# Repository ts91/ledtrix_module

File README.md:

# Ledtrix, a fully modular 16x16 LED matrix

Tileable and low profile (less than 1cm) for display applications. Can be used in an artsy clock. Each single LED is source/sink driven by a pair of transistors.

The transistors are controlled by shift-registers. There are 4 daisy-chained shift-registers with each 8 outputs giving the required 16 rows and 16 columns drive signals.

## Tileable
The outline of the unit is the same as 4 LED modules in a 2x2 configuration. This makes it possible to seamlessly tile the Ledtrix along any of its four edges.

Signals travel through the board from the left to the right indicated by the arrow and socket. The boards are soldered together by edge connectors. Soldering all of these gives a sturdy unit.

### Mounting holes
There are four mount holes on the back. It is impossible to reach these holes once the LED modules have been soldered onto the PCB. They can be used with press fit mount stages.

## Driving the Ledtrix
This can be tricky as the focus has been to make the PCB routing as simple as possible. Some thought must be put into it.
## Pictures

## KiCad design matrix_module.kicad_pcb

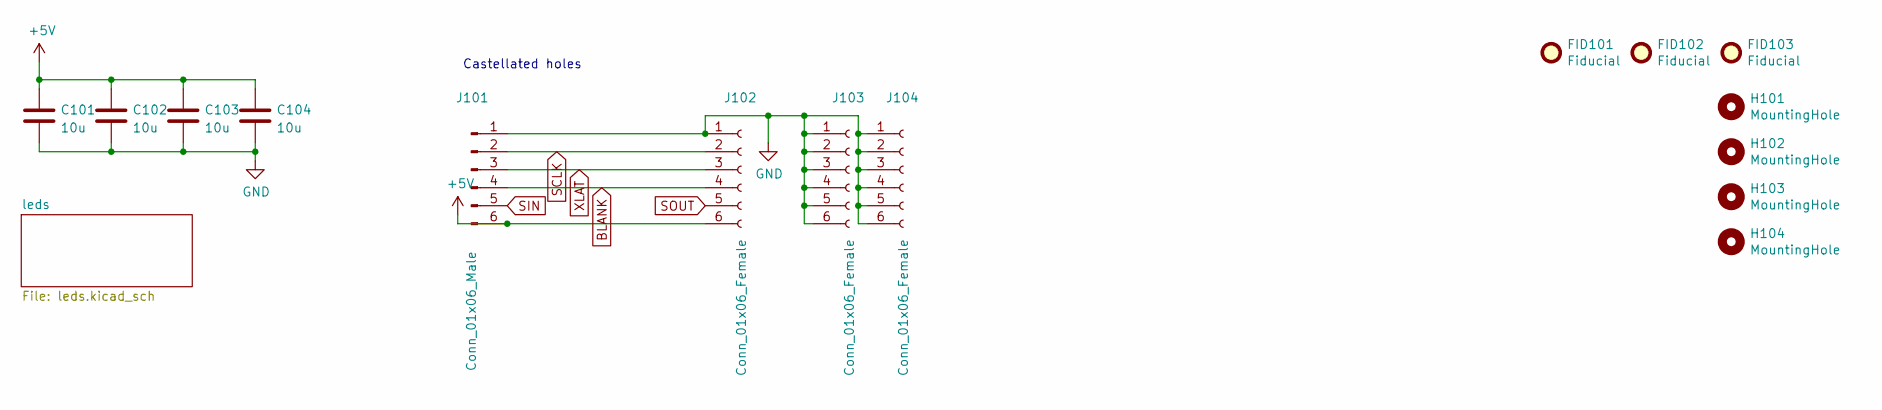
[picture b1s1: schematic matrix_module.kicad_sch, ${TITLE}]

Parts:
C101, C102, C103, C104: 10u; C_0805_2012Metric
FID101, FID102, FID103: Fiducial; Fiducial_0.5mm_Dia_1mm_Outer
H101, H102, H103, H104: MountingHole; MountingHole_2.2mm_M2
J101: Conn_01x06_Male; CastellatedEdge_1x06P3.175mm_Vertical
J102, J103, J104: Conn_01x06_Female; CastellatedEdge_1x06P3.175mm_Vertical

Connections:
+5V: C101.1, C102.1, C103.1, C104.1, J101.6, J102.6; also elsewhere on the board
BLANK: J101.4, J102.4; also elsewhere on the board
GND: C101.2, C102.2, C103.2, C104.2, J101.1, J102.1, J103.1, J103.2, J103.3, J103.4, J103.5, J103.6, J104.1, J104.2, J104.3, J104.4, J104.5, J104.6; also elsewhere on the board
SCLK: J101.2, J102.2; also elsewhere on the board
SIN: J101.5; also elsewhere on the board
SOUT: J102.5; also elsewhere on the board
XLAT: J101.3, J102.3; also elsewhere on the board

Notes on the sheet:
Castellated holes

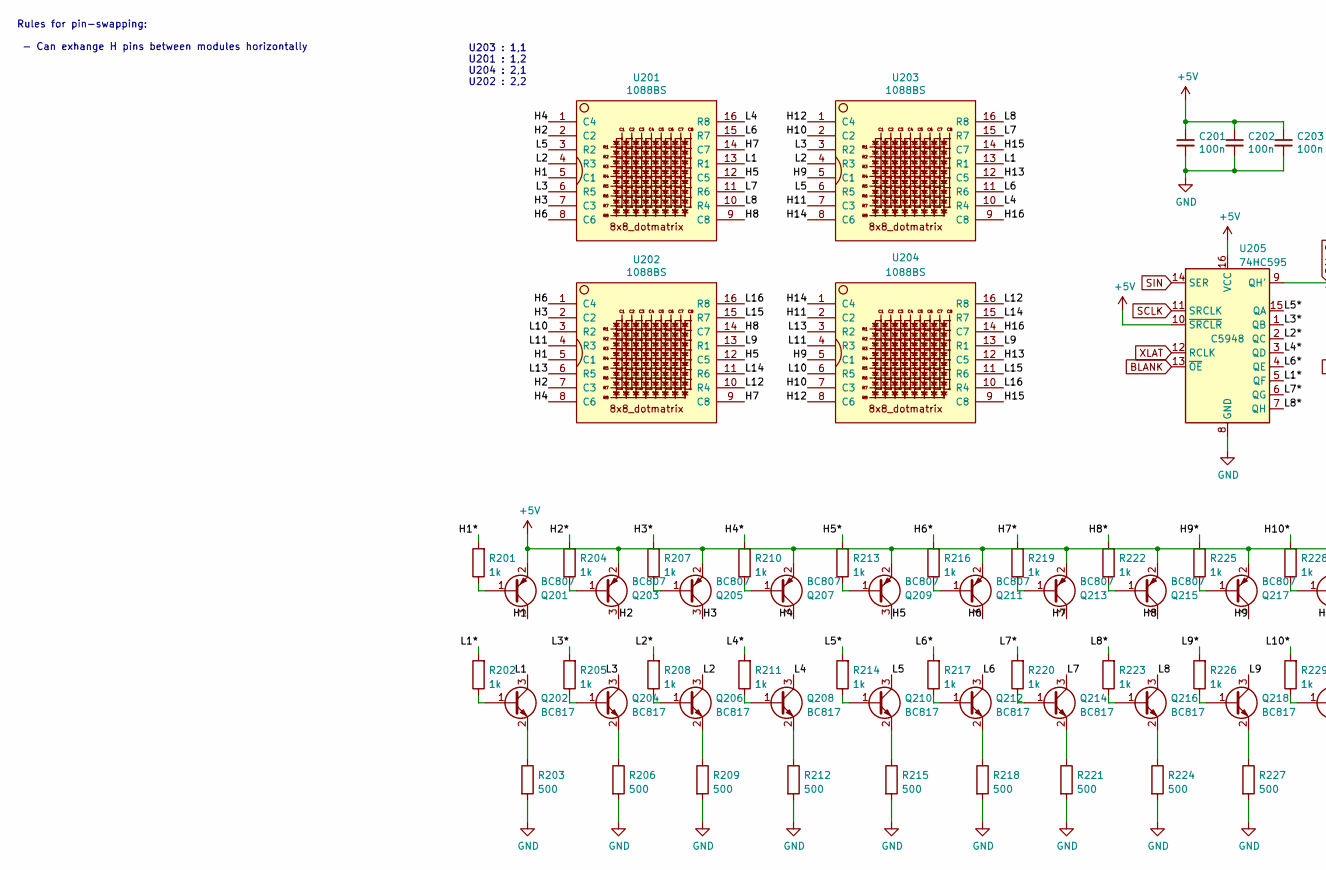
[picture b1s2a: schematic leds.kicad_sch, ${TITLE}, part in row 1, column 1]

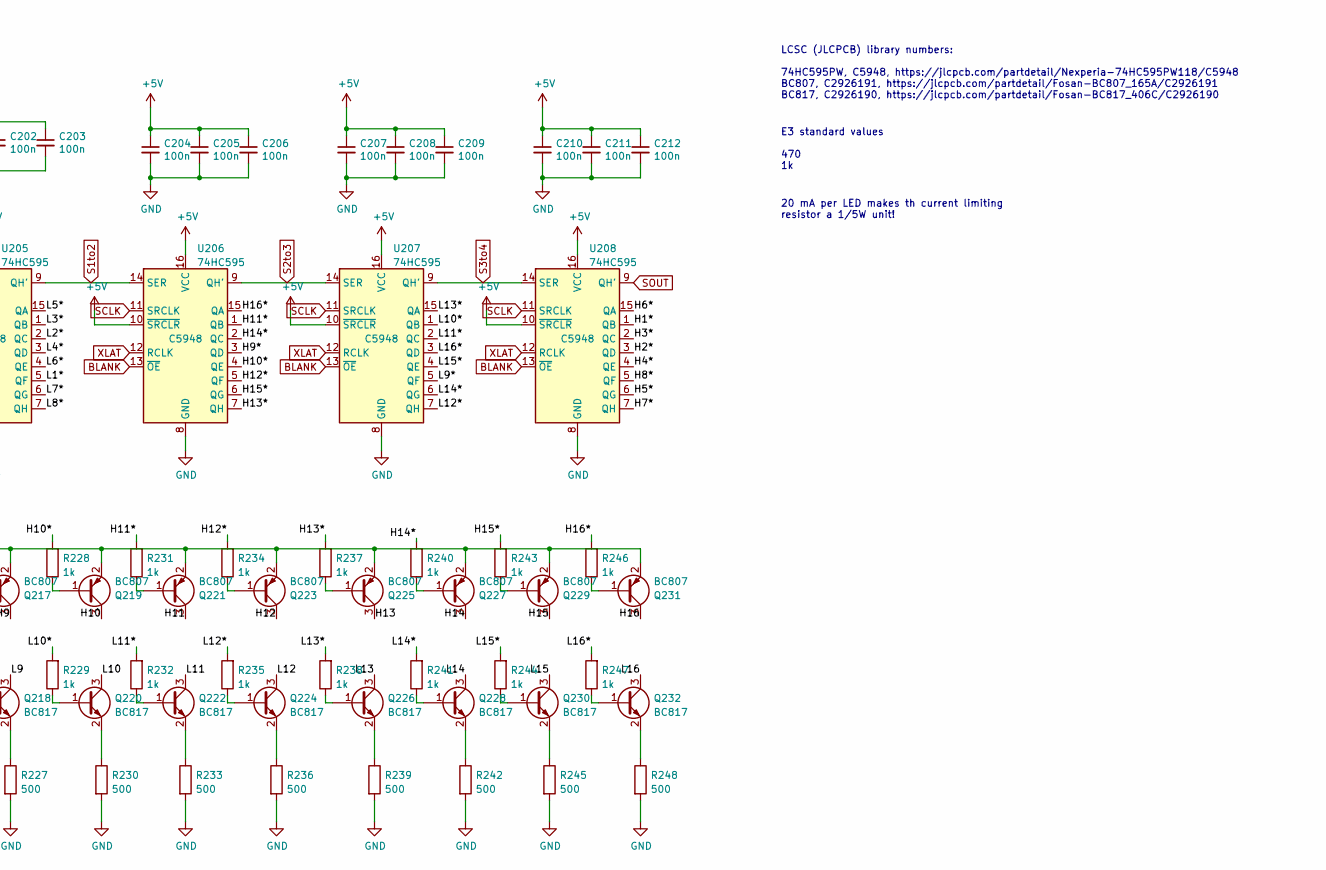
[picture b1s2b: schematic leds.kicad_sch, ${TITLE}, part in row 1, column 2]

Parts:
C201, C202, C203, C204, C205, C206, C207, C208, C209, C210, C211, C212: 100n; C_0603_1608Metric
Q201, Q203, Q205, Q207, Q209, Q211, Q213, Q215, Q217, Q219, Q221, Q223, Q225, Q227, Q229, Q231: BC807; SOT-23
Q202, Q204, Q206, Q208, Q210, Q212, Q214, Q216, Q218, Q220, Q222, Q224, Q226, Q228, Q230, Q232: BC817; SOT-23
R201, R202, R204, R205, R207, R208, R210, R211, R213, R214, R216, R217, R219, R220, R222, R223, R225, R226, R228, R229, R231, R232, R234, R235, R237, R238, R240, R241, R243, R244, R246, R247: 1k; R_0603_1608Metric
R203, R206, R209, R212, R215, R218, R221, R224, R227, R230, R233, R236, R239, R242, R245, R248: 500; R_0603_1608Metric
U201, U202, U203, U204: 1088BS; 8x8_dotmatrix_1088
U205, U206, U207, U208: 74HC595; TSSOP-16_4.4x5mm_P0.65mm; LCSC C5948

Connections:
+5V: C201.1, C202.1, C203.1, C204.1, C205.1, C206.1, C207.1, C208.1, C209.1, C210.1, C211.1, C212.1, Q201.2 (E), Q203.2 (E), Q205.2 (E), Q207.2 (E), Q209.2 (E), Q211.2 (E), Q213.2 (E), Q215.2 (E), Q217.2 (E), Q219.2 (E), Q221.2 (E), Q223.2 (E), Q225.2 (E), Q227.2 (E), Q229.2 (E), Q231.2 (E), U205.10 (~SRCLR), U205.16 (VCC), U206.10 (~SRCLR), U206.16 (VCC), U207.10 (~SRCLR), U207.16 (VCC), U208.10 (~SRCLR), U208.16 (VCC); also elsewhere on the board
/leds/H1: Q201.3 (C), U201.5 (C1), U202.5 (C1)
/leds/H1*: R201.2, U208.1 (QB)
/leds/H2: Q203.3 (C), U201.2 (C2), U202.7 (C3)
/leds/H2*: R204.2, U208.3 (QD)
/leds/H3: Q205.3 (C), U201.7 (C3), U202.2 (C2)
/leds/H3*: R207.2, U208.2 (QC)
/leds/H4: Q207.3 (C), U201.1 (C4), U202.8 (C6)
/leds/H4*: R210.2, U208.4 (QE)
/leds/H5: Q209.3 (C), U201.12 (C5), U202.12 (C5)
/leds/H5*: R213.2, U208.6 (QG)
/leds/H6: Q211.3 (C), U201.8 (C6), U202.1 (C4)
/leds/H6*: R216.2, U208.15 (QA)
/leds/H7: Q213.3 (C), U201.14 (C7), U202.9 (C8)
/leds/H7*: R219.2, U208.7 (QH)
/leds/H8: Q215.3 (C), U201.9 (C8), U202.14 (C7)
/leds/H8*: R222.2, U208.5 (QF)
/leds/H9: Q217.3 (C), U203.5 (C1), U204.5 (C1)
/leds/H9*: R225.2, U206.3 (QD)
/leds/H10: Q219.3 (C), U203.2 (C2), U204.7 (C3)
/leds/H10*: R228.2, U206.4 (QE)
/leds/H11: Q221.3 (C), U203.7 (C3), U204.2 (C2)
/leds/H11*: R231.2, U206.1 (QB)
/leds/H12: Q223.3 (C), U203.1 (C4), U204.8 (C6)
/leds/H12*: R234.2, U206.5 (QF)
/leds/H13: Q225.3 (C), U203.12 (C5), U204.12 (C5)
/leds/H13*: R237.2, U206.7 (QH)
/leds/H14: Q227.3 (C), U203.8 (C6), U204.1 (C4)
/leds/H14*: R240.2, U206.2 (QC)
/leds/H15: Q229.3 (C), U203.14 (C7), U204.9 (C8)
/leds/H15*: R243.2, U206.6 (QG)
/leds/H16: Q231.3 (C), U203.9 (C8), U204.14 (C7)
/leds/H16*: R246.2, U206.15 (QA)
/leds/L1: Q202.3 (C), U201.13 (R1), U203.13 (R1)
/leds/L1*: R202.2, U205.5 (QF)
/leds/L2: Q206.3 (C), U201.4 (R3), U203.4 (R3)
/leds/L2*: R208.2, U205.2 (QC)
/leds/L3: Q204.3 (C), U201.6 (R5), U203.3 (R2)
/leds/L3*: R205.2, U205.1 (QB)
/leds/L4: Q208.3 (C), U201.16 (R8), U203.10 (R4)
/leds/L4*: R211.2, U205.3 (QD)
/leds/L5: Q210.3 (C), U201.3 (R2), U203.6 (R5)
/leds/L5*: R214.2, U205.15 (QA)
/leds/L6: Q212.3 (C), U201.15 (R7), U203.11 (R6)
/leds/L6*: R217.2, U205.4 (QE)
/leds/L7: Q214.3 (C), U201.11 (R6), U203.15 (R7)
/leds/L7*: R220.2, U205.6 (QG)
/leds/L8: Q216.3 (C), U201.10 (R4), U203.16 (R8)
/leds/L8*: R223.2, U205.7 (QH)
/leds/L9: Q218.3 (C), U202.13 (R1), U204.13 (R1)
/leds/L9*: R226.2, U207.5 (QF)
/leds/L10: Q220.3 (C), U202.3 (R2), U204.6 (R5)
/leds/L10*: R229.2, U207.1 (QB)
/leds/L11: Q222.3 (C), U202.4 (R3), U204.4 (R3)
/leds/L11*: R232.2, U207.2 (QC)
/leds/L12: Q224.3 (C), U202.10 (R4), U204.16 (R8)
/leds/L12*: R235.2, U207.7 (QH)
/leds/L13: Q226.3 (C), U202.6 (R5), U204.3 (R2)
/leds/L13*: R238.2, U207.15 (QA)
/leds/L14: Q228.3 (C), U202.11 (R6), U204.15 (R7)
/leds/L14*: R241.2, U207.6 (QG)
/leds/L15: Q230.3 (C), U202.15 (R7), U204.11 (R6)
/leds/L15*: R244.2, U207.4 (QE)
/leds/L16: Q232.3 (C), U202.16 (R8), U204.10 (R4)
/leds/L16*: R247.2, U207.3 (QD)
BLANK: U205.13 (~OE), U206.13 (~OE), U207.13 (~OE), U208.13 (~OE); also elsewhere on the board
GND: C201.2, C202.2, C203.2, C204.2, C205.2, C206.2, C207.2, C208.2, C209.2, C210.2, C211.2, C212.2, R203.2, R206.2, R209.2, R212.2, R215.2, R218.2, R221.2, R224.2, R227.2, R230.2, R233.2, R236.2, R239.2, R242.2, R245.2, R248.2, U205.8 (GND), U206.8 (GND), U207.8 (GND), U208.8 (GND); also elsewhere on the board
unnamed: Q201.1 (B), R201.1
unnamed: Q202.1 (B), R202.1
unnamed: Q202.2 (E), R203.1
unnamed: Q203.1 (B), R204.1
unnamed: Q204.1 (B), R205.1
unnamed: Q204.2 (E), R206.1
unnamed: Q205.1 (B), R207.1
unnamed: Q206.1 (B), R208.1
unnamed: Q206.2 (E), R209.1
unnamed: Q207.1 (B), R210.1
unnamed: Q208.1 (B), R211.1
unnamed: Q208.2 (E), R212.1
unnamed: Q209.1 (B), R213.1
unnamed: Q210.1 (B), R214.1
unnamed: Q210.2 (E), R215.1
unnamed: Q211.1 (B), R216.1
unnamed: Q212.1 (B), R217.1
unnamed: Q212.2 (E), R218.1
unnamed: Q213.1 (B), R219.1
unnamed: Q214.1 (B), R220.1
unnamed: Q214.2 (E), R221.1
unnamed: Q215.1 (B), R222.1
unnamed: Q216.1 (B), R223.1
unnamed: Q216.2 (E), R224.1
unnamed: Q217.1 (B), R225.1
unnamed: Q218.1 (B), R226.1
unnamed: Q218.2 (E), R227.1
unnamed: Q219.1 (B), R228.1
unnamed: Q220.1 (B), R229.1
unnamed: Q220.2 (E), R230.1
unnamed: Q221.1 (B), R231.1
unnamed: Q222.1 (B), R232.1
unnamed: Q222.2 (E), R233.1
unnamed: Q223.1 (B), R234.1
unnamed: Q224.1 (B), R235.1
unnamed: Q224.2 (E), R236.1
unnamed: Q225.1 (B), R237.1
unnamed: Q226.1 (B), R238.1
unnamed: Q226.2 (E), R239.1
unnamed: Q227.1 (B), R240.1
unnamed: Q228.1 (B), R241.1
unnamed: Q228.2 (E), R242.1
unnamed: Q229.1 (B), R243.1
unnamed: Q230.1 (B), R244.1
unnamed: Q230.2 (E), R245.1
unnamed: Q231.1 (B), R246.1
unnamed: Q232.1 (B), R247.1
unnamed: Q232.2 (E), R248.1
S1to2: U205.9 (QH'), U206.14 (SER)
S2to3: U206.9 (QH'), U207.14 (SER)
S3to4: U207.9 (QH'), U208.14 (SER)
SCLK: U205.11 (SRCLK), U206.11 (SRCLK), U207.11 (SRCLK), U208.11 (SRCLK); also elsewhere on the board
SIN: U205.14 (SER); also elsewhere on the board
SOUT: U208.9 (QH'); also elsewhere on the board
XLAT: U205.12 (RCLK), U206.12 (RCLK), U207.12 (RCLK), U208.12 (RCLK); also elsewhere on the board

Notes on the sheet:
E3 standard values 470 1k
U203 : 1,1 U201 : 1,2 U204 : 2,1 U202 : 2,2
20 mA per LED makes th current limiting resistor a 1/5W unit!
Rules for pin-swapping: - Can exhange H pins between modules horizontally
LCSC (JLCPCB) library numbers: 74HC595PW, C5948, https://jlcpcb.com/partdetail/Nexperia-74HC595PW118/C5948 BC807, C2926191, https://jlcpcb.com/partdetail/Fosan-BC807_165A/C2926191 BC817, C2926190, https://jlcpcb.com/partdetail/Fosan-BC817_406C/C2926190

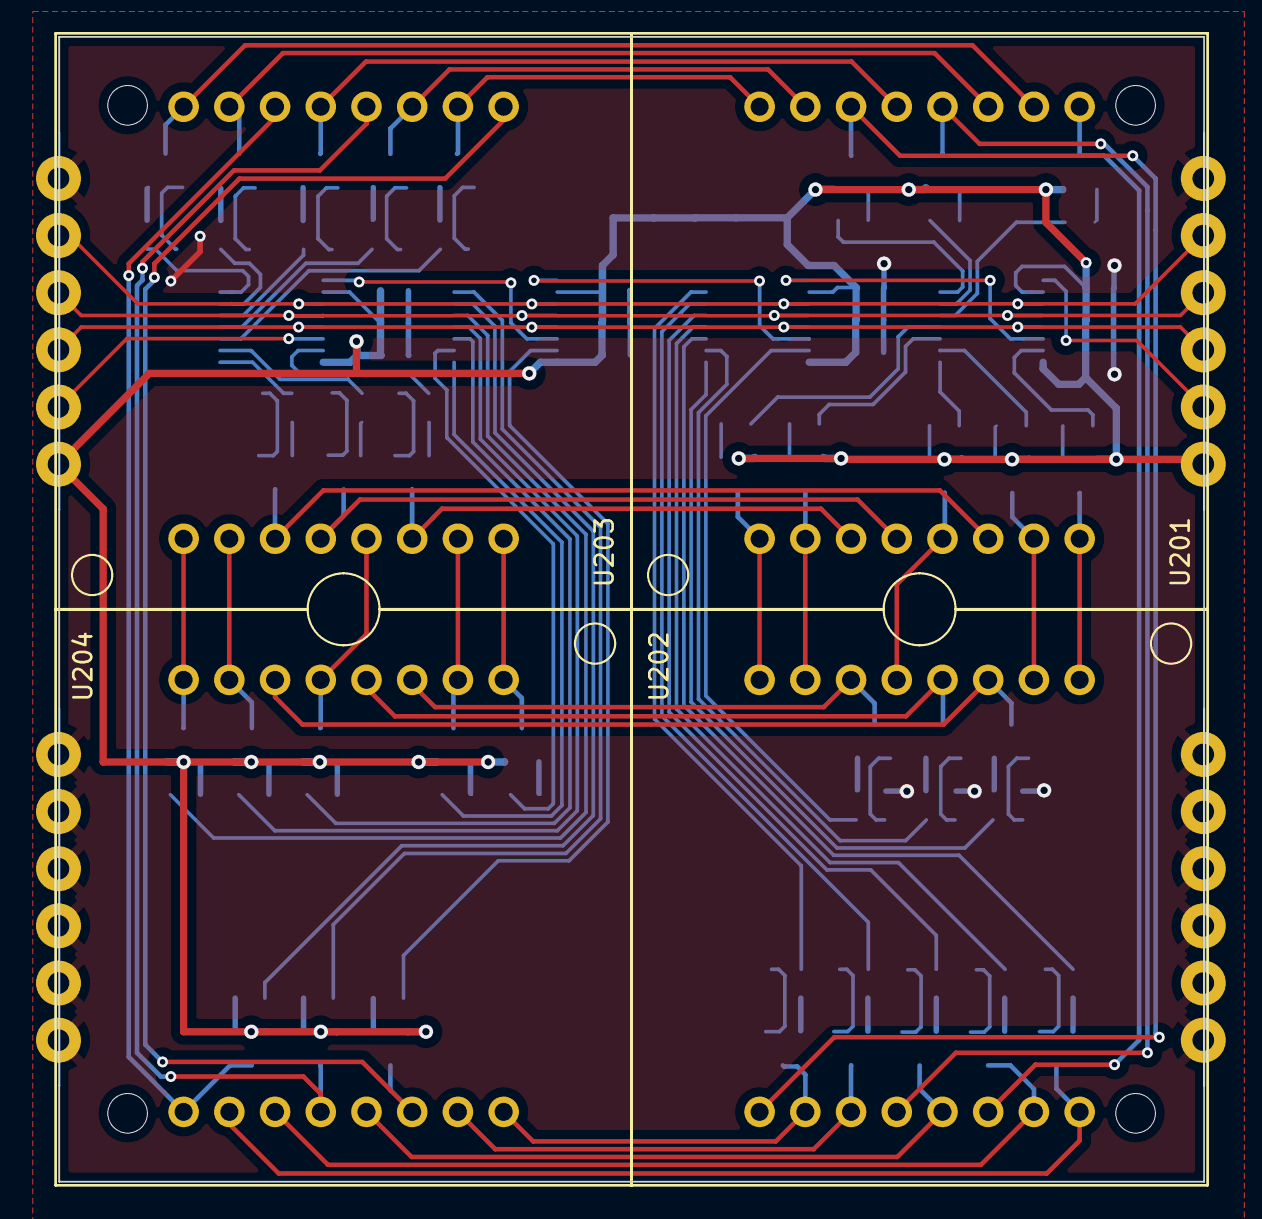
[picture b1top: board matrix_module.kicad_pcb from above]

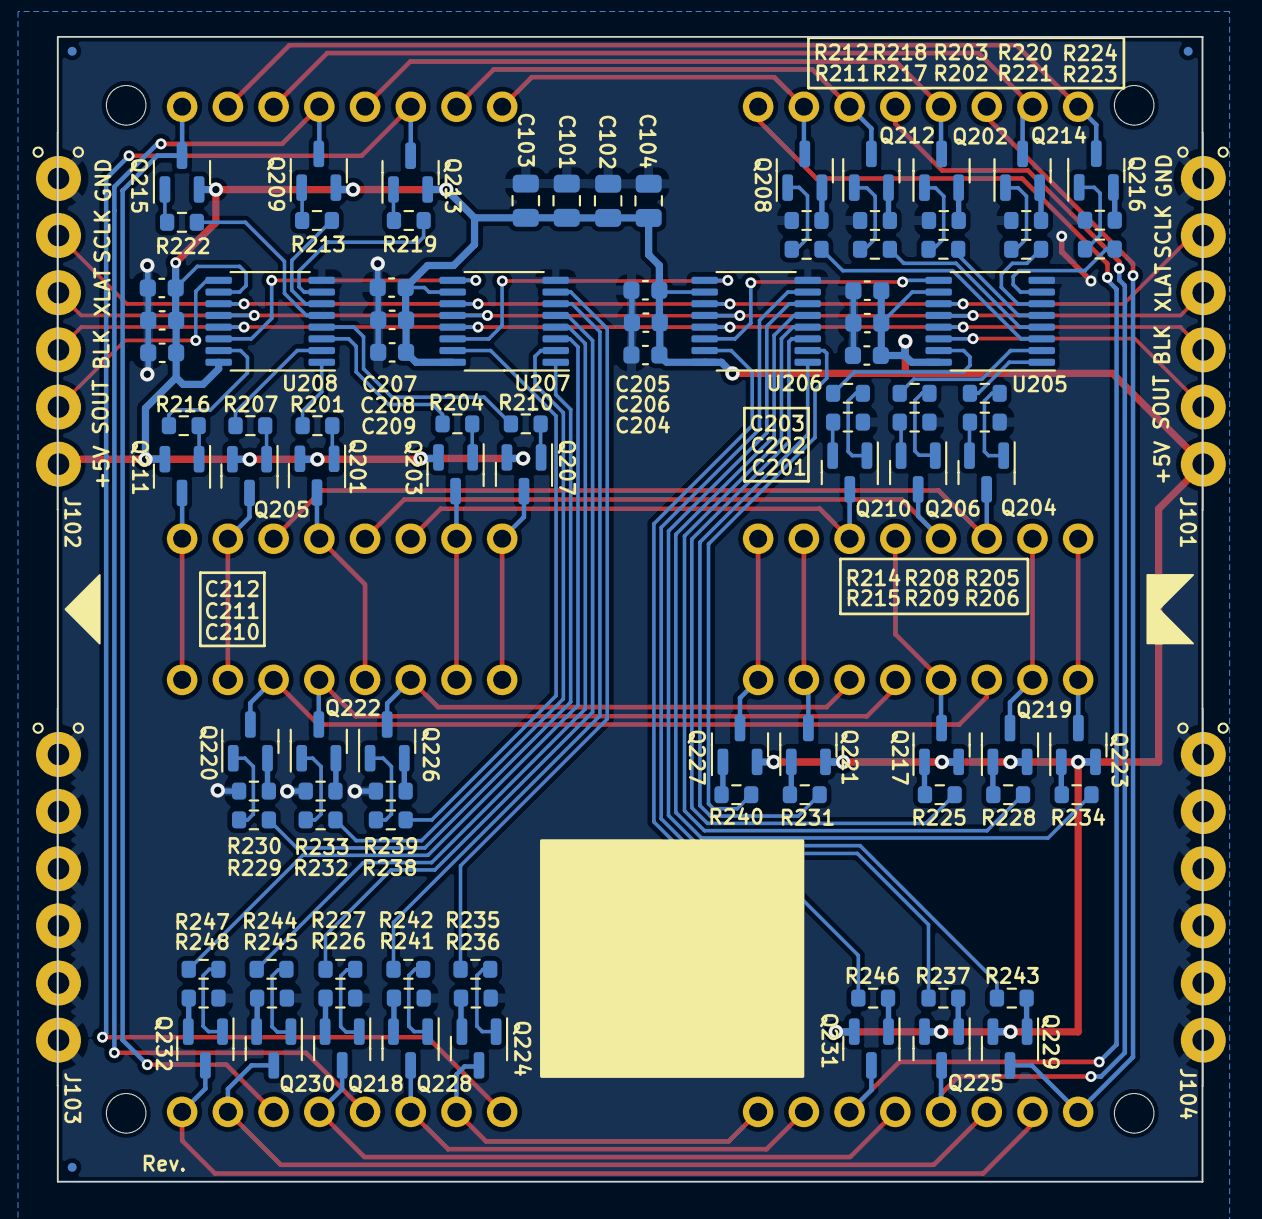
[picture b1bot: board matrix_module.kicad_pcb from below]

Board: 2 copper layers, 63.6 x 63.6 mm, 115 parts (107 on the bottom side), 122 nets.

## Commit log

2023-10-22 Add KiCad project files
